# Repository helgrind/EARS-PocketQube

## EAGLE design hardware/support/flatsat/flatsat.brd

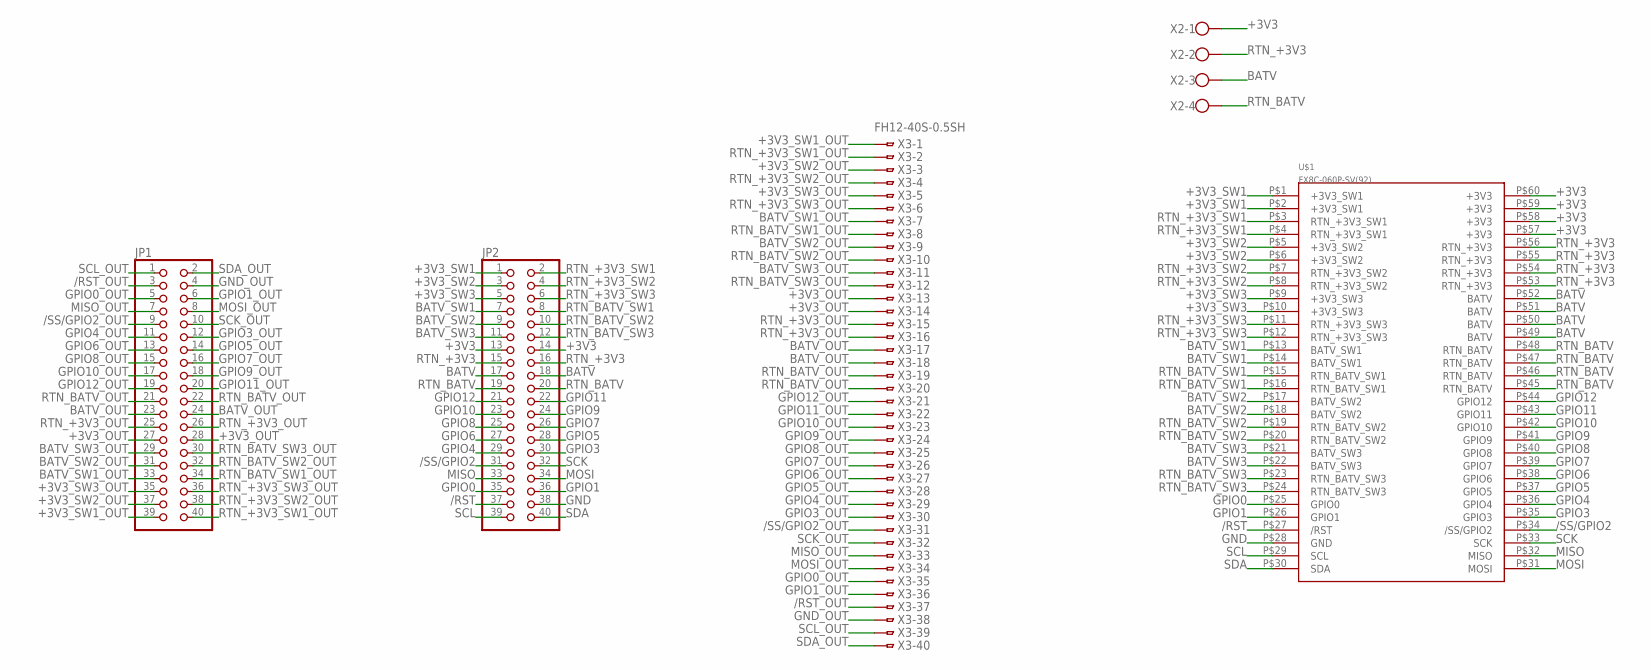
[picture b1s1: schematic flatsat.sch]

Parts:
JP1, JP2: PINHD-2X20/90; 2X20/90
U$1: FX8C-060P-SV(92)
X2: W237-4
X3: FH12-40S-0.5SH

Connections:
+3V3: JP2.13, JP2.14, U$1.P$57 (+3V3), U$1.P$58 (+3V3), U$1.P$59 (+3V3), U$1.P$60 (+3V3), X2.1
+3V3_OUT: JP1.27, JP1.28, X3.13, X3.14
+3V3_SW1: JP2.1, U$1.P$1 (+3V3_SW1), U$1.P$2 (+3V3_SW1)
+3V3_SW1_OUT: JP1.39, X3.1
+3V3_SW2: JP2.3, U$1.P$5 (+3V3_SW2), U$1.P$6 (+3V3_SW2)
+3V3_SW2_OUT: JP1.37, X3.3
+3V3_SW3: JP2.5, U$1.P$9 (+3V3_SW3), U$1.P$10 (+3V3_SW3)
+3V3_SW3_OUT: JP1.35, X3.5
/RST: JP2.37, U$1.P$27 (/RST)
/RST_OUT: JP1.3, X3.37
/SS/GPIO2: JP2.31, U$1.P$34 (/SS/GPIO2)
/SS/GPIO2_OUT: JP1.9, X3.31
BATV: JP2.17, JP2.18, U$1.P$49 (BATV), U$1.P$50 (BATV), U$1.P$51 (BATV), U$1.P$52 (BATV), X2.3
BATV_OUT: JP1.23, JP1.24, X3.17, X3.18
BATV_SW1: JP2.7, U$1.P$13 (BATV_SW1), U$1.P$14 (BATV_SW1)
BATV_SW1_OUT: JP1.33, X3.7
BATV_SW2: JP2.9, U$1.P$17 (BATV_SW2), U$1.P$18 (BATV_SW2)
BATV_SW2_OUT: JP1.31, X3.9
BATV_SW3: JP2.11, U$1.P$21 (BATV_SW3), U$1.P$22 (BATV_SW3)
BATV_SW3_OUT: JP1.29, X3.11
GND: JP2.38, U$1.P$28 (GND)
GND_OUT: JP1.4, X3.38
GPIO0: JP2.35, U$1.P$25 (GPIO0)
GPIO0_OUT: JP1.5, X3.35
GPIO1: JP2.36, U$1.P$26 (GPIO1)
GPIO1_OUT: JP1.6, X3.36
GPIO3: JP2.30, U$1.P$35 (GPIO3)
GPIO3_OUT: JP1.12, X3.30
GPIO4: JP2.29, U$1.P$36 (GPIO4)
GPIO4_OUT: JP1.11, X3.29
GPIO5: JP2.28, U$1.P$37 (GPIO5)
GPIO5_OUT: JP1.14, X3.28
GPIO6: JP2.27, U$1.P$38 (GPIO6)
GPIO6_OUT: JP1.13, X3.27
GPIO7: JP2.26, U$1.P$39 (GPIO7)
GPIO7_OUT: JP1.16, X3.26
GPIO8: JP2.25, U$1.P$40 (GPIO8)
GPIO8_OUT: JP1.15, X3.25
GPIO9: JP2.24, U$1.P$41 (GPIO9)
GPIO9_OUT: JP1.18, X3.24
GPIO10: JP2.23, U$1.P$42 (GPIO10)
GPIO10_OUT: JP1.17, X3.23
GPIO11: JP2.22, U$1.P$43 (GPIO11)
GPIO11_OUT: JP1.20, X3.22
GPIO12: JP2.21, U$1.P$44 (GPIO12)
GPIO12_OUT: JP1.19, X3.21
MISO: JP2.33, U$1.P$32 (MISO)
MISO_OUT: JP1.7, X3.33
MOSI: JP2.34, U$1.P$31 (MOSI)
MOSI_OUT: JP1.8, X3.34
RTN_+3V3: JP2.15, JP2.16, U$1.P$53 (RTN_+3V3), U$1.P$54 (RTN_+3V3), U$1.P$55 (RTN_+3V3), U$1.P$56 (RTN_+3V3), X2.2
RTN_+3V3_OUT: JP1.25, JP1.26, X3.15, X3.16
RTN_+3V3_SW1: JP2.2, U$1.P$3 (RTN_+3V3_SW1), U$1.P$4 (RTN_+3V3_SW1)
RTN_+3V3_SW1_OUT: JP1.40, X3.2
RTN_+3V3_SW2: JP2.4, U$1.P$7 (RTN_+3V3_SW2), U$1.P$8 (RTN_+3V3_SW2)
RTN_+3V3_SW2_OUT: JP1.38, X3.4
RTN_+3V3_SW3: JP2.6, U$1.P$11 (RTN_+3V3_SW3), U$1.P$12 (RTN_+3V3_SW3)
RTN_+3V3_SW3_OUT: JP1.36, X3.6
RTN_BATV: JP2.19, JP2.20, U$1.P$45 (RTN_BATV), U$1.P$46 (RTN_BATV), U$1.P$47 (RTN_BATV), U$1.P$48 (RTN_BATV), X2.4
RTN_BATV_OUT: JP1.21, JP1.22, X3.19, X3.20
RTN_BATV_SW1: JP2.8, U$1.P$15 (RTN_BATV_SW1), U$1.P$16 (RTN_BATV_SW1)
RTN_BATV_SW1_OUT: JP1.34, X3.8
RTN_BATV_SW2: JP2.10, U$1.P$19 (RTN_BATV_SW2), U$1.P$20 (RTN_BATV_SW2)
RTN_BATV_SW2_OUT: JP1.32, X3.10
RTN_BATV_SW3: JP2.12, U$1.P$23 (RTN_BATV_SW3), U$1.P$24 (RTN_BATV_SW3)
RTN_BATV_SW3_OUT: JP1.30, X3.12
SCK: JP2.32, U$1.P$33 (SCK)
SCK_OUT: JP1.10, X3.32
SCL: JP2.39, U$1.P$29 (SCL)
SCL_OUT: JP1.1, X3.39
SDA: JP2.40, U$1.P$30 (SDA)
SDA_OUT: JP1.2, X3.40

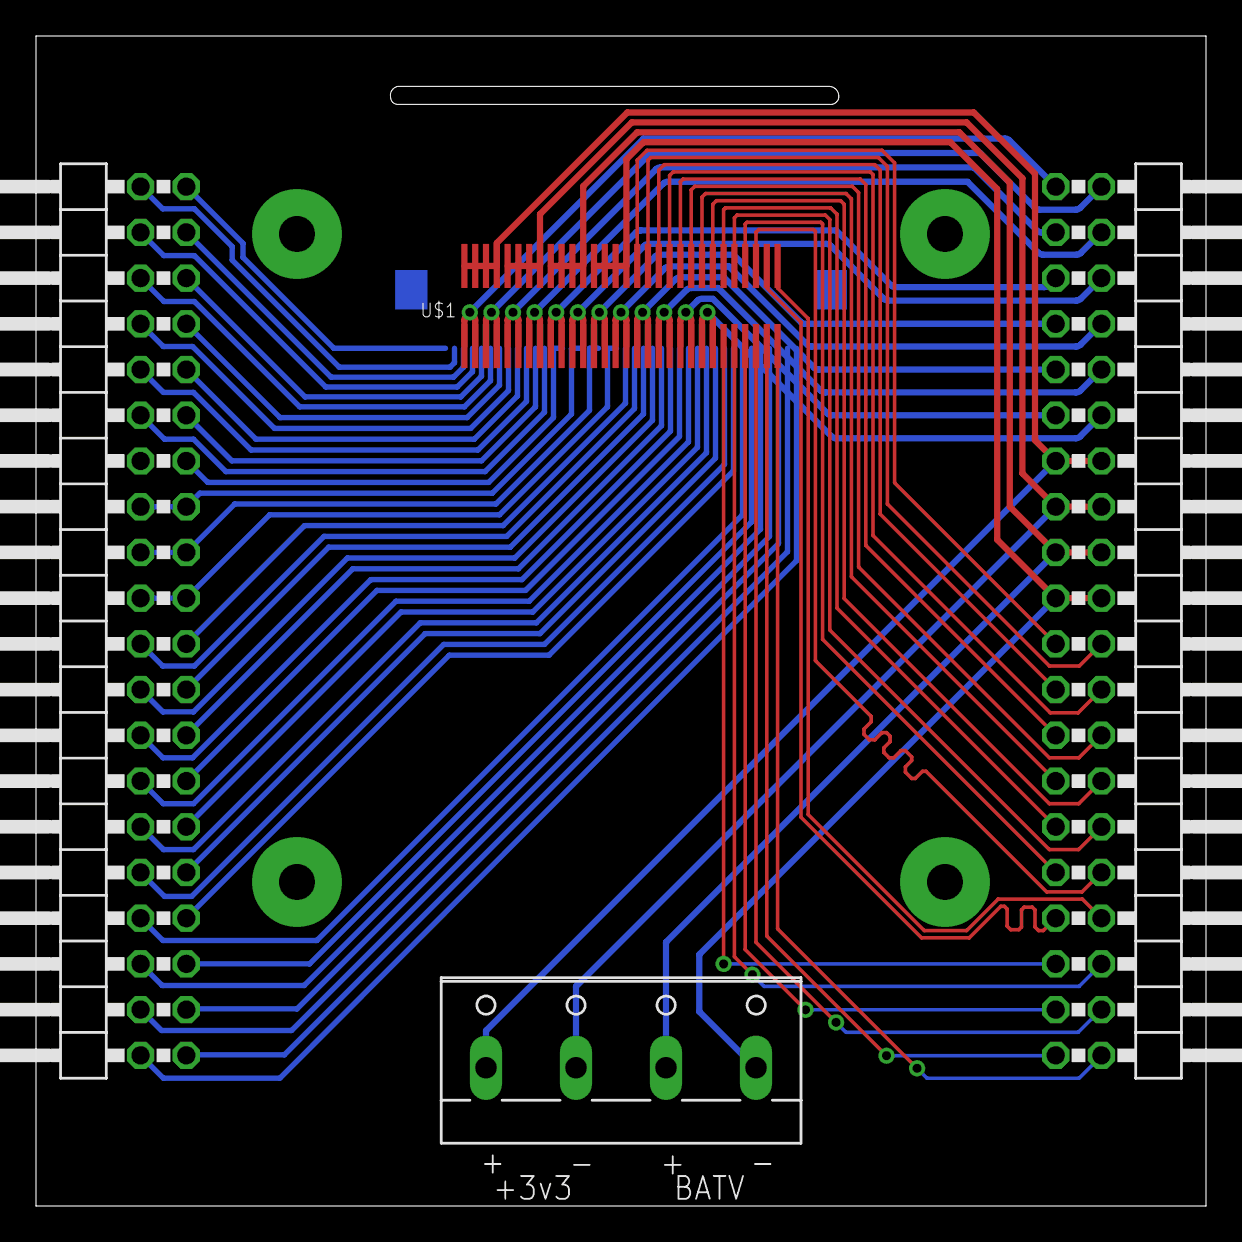
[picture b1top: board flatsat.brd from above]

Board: 2 copper layers, 65.0 x 65.0 mm, 5 parts (1 on the bottom side), 72 nets.

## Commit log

2015-06-20 added adapter board
2015-06-20 merged master updates
2015-06-20 added flatsat board and routed
